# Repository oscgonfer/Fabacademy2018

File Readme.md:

# Fabacademy 2018

This repository is meant to host the week assignments for the fabacademy 2018.

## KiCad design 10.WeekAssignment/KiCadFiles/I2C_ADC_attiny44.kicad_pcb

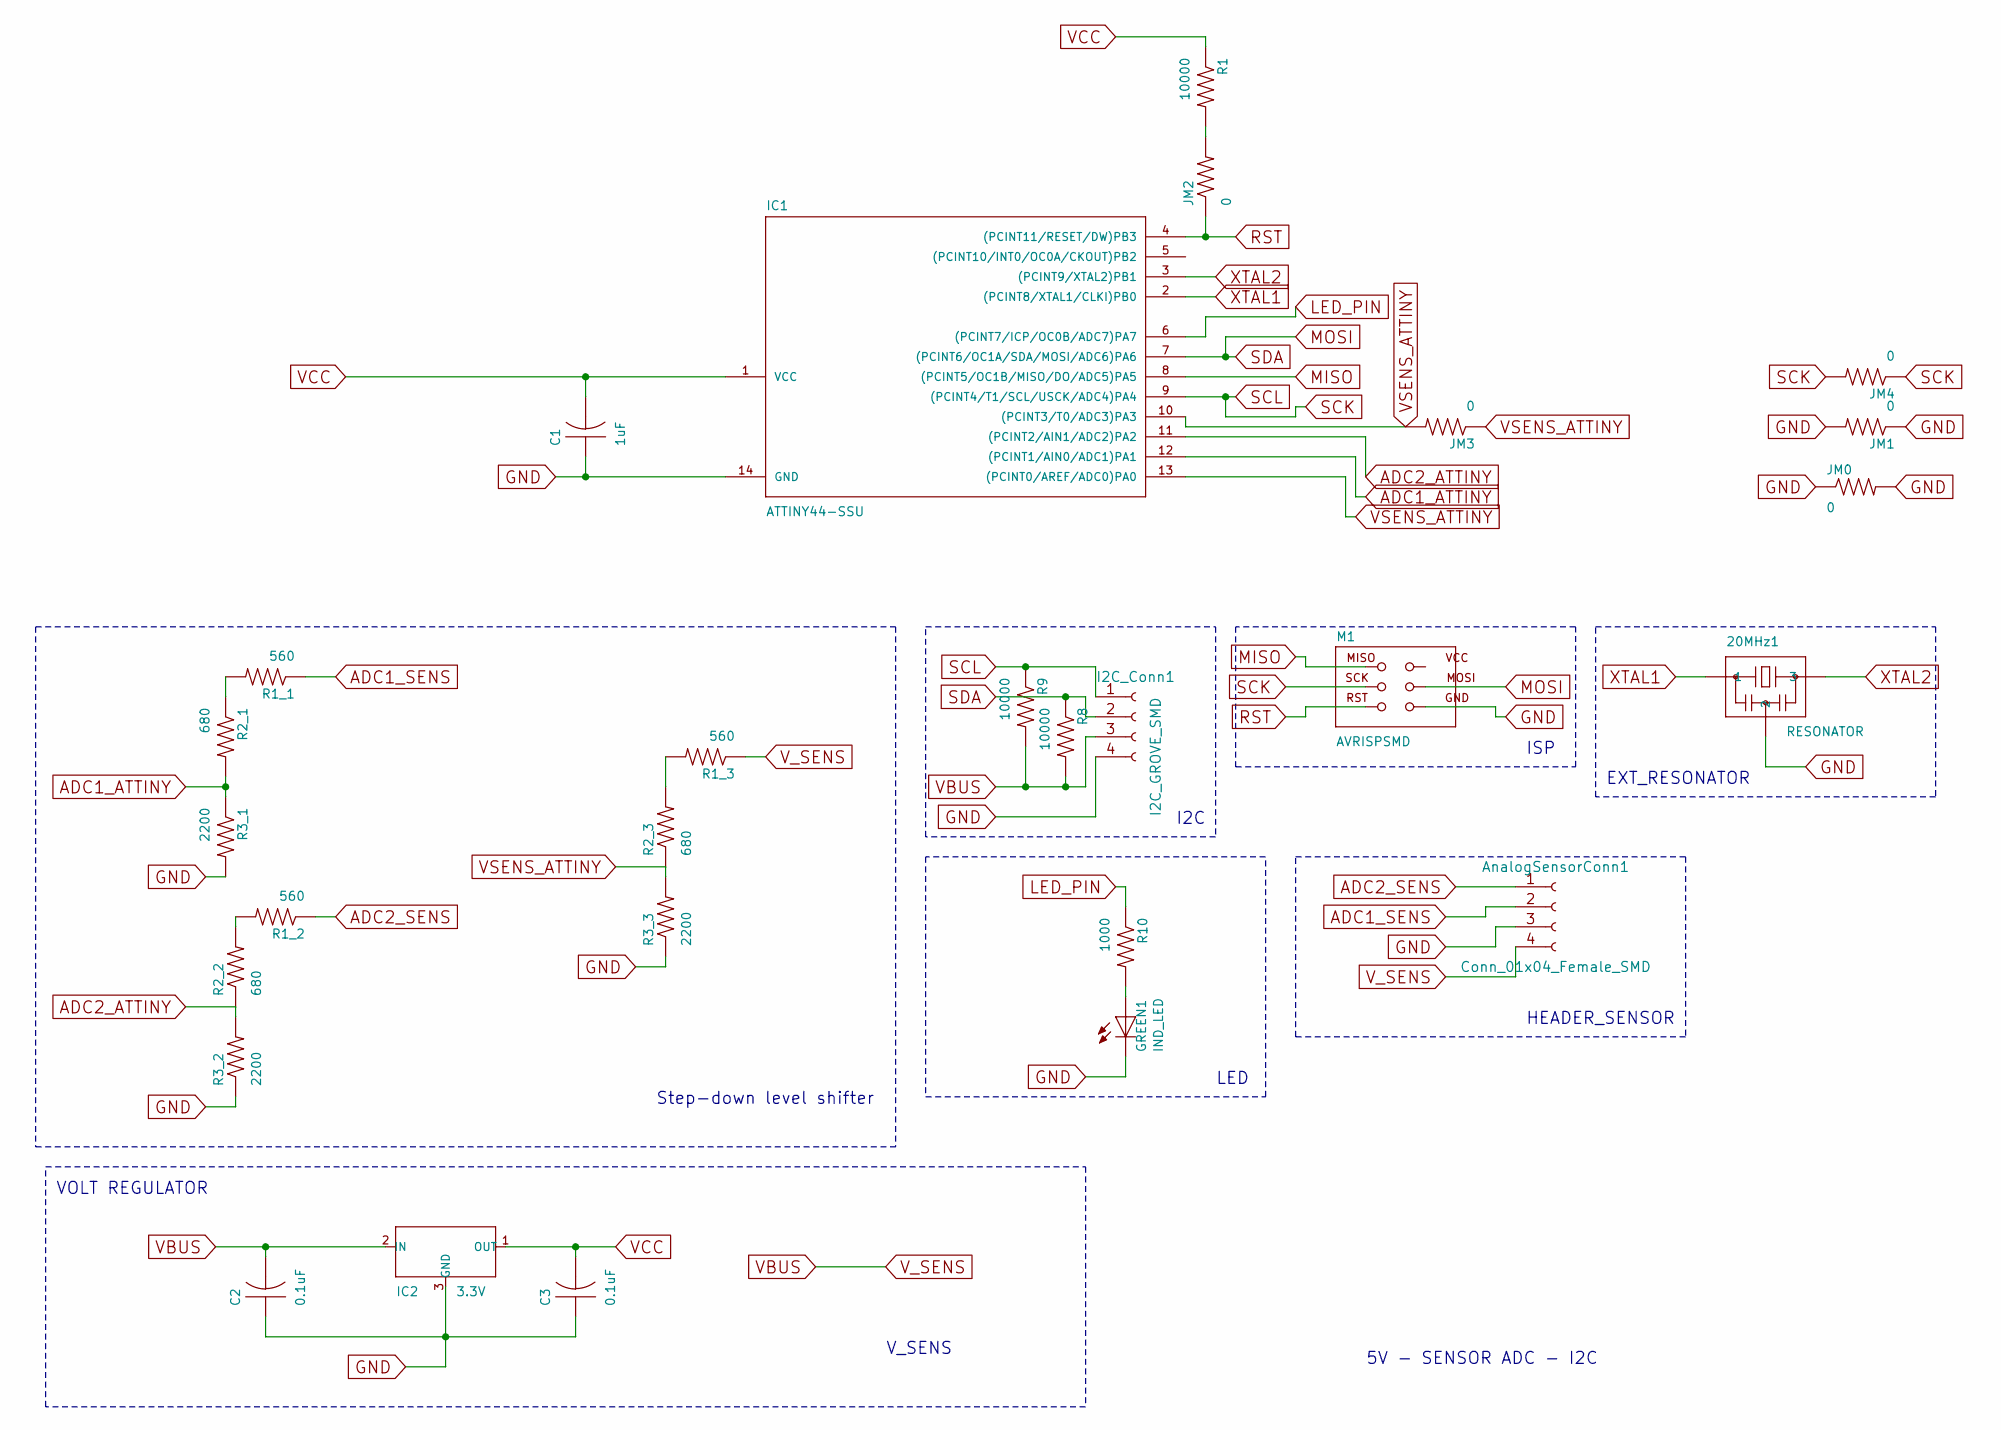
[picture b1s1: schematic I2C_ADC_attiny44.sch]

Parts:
20MHz1: RESONATOR; fab-EFOBM
AnalogSensorConn1: Conn_01x04_Female_SMD; 1X04SMD
C1: 1uF; fab_C1206FAB
C2, C3: 0.1uF; fab-C1206FAB
GREEN1: IND_LED; fab-LED1206FAB
I2C_Conn1: I2C_GROVE_SMD; I2C_GROVE
IC1: ATTINY44-SSU; fab-SOIC14
IC2: 3.3V; fab-SOT23
JM0, JM1, JM2, JM3, JM4: 0; fab-R1206FAB
M1: AVRISPSMD; fab-2X03SMD
R1, R8, R9: 10000; fab-R1206FAB
R1_1, R1_2, R1_3: 560; fab-R1206FAB
R2_1: 680; fab_R1206FAB
R2_2, R2_3: 680; fab-R1206FAB
R3_1, R3_2, R3_3: 2200; fab-R1206FAB
R10: 1000; fab-R1206FAB

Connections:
ADC1_ATTINY: IC1.12 ((PCINT1/AIN0/ADC1)PA1), R2_1.2, R3_1.1
ADC1_SENS: AnalogSensorConn1.2, R1_1.1
ADC2_ATTINY: IC1.11 ((PCINT2/AIN1/ADC2)PA2), R2_2.1, R3_2.2
ADC2_SENS: AnalogSensorConn1.1, R1_2.1
GND: 20MHz1.2, AnalogSensorConn1.3, C1.1, C2.1, C3.1, GREEN1.2 (C), I2C_Conn1.4, IC1.14 (GND), IC2.3 (GND), JM0.1, JM0.2, JM1.1, JM1.2, M1.6 (GND), R3_1.2, R3_2.1, R3_3.1
LED_PIN: IC1.6 ((PCINT7/ICP/OC0B/ADC7)PA7), R10.1
MISO: IC1.8 ((PCINT5/OC1B/MISO/DO/ADC5)PA5), M1.1 (MISO)
MOSI: I2C_Conn1.2, IC1.7 ((PCINT6/OC1A/SDA/MOSI/ADC6)PA6), M1.4 (MOSI), R8.1
unnamed: GREEN1.1 (A), R10.2
unnamed: JM2.2, R1.2
unnamed: R1_1.2, R2_1.1
unnamed: R1_2.2, R2_2.2
unnamed: R1_3.2, R2_3.2
RST: IC1.4 ((PCINT11/RESET/DW)PB3), JM2.1, M1.5 (RST)
SCK: I2C_Conn1.1, IC1.9 ((PCINT4/T1/SCL/USCK/ADC4)PA4), JM4.1, JM4.2, M1.3 (SCK), R9.1
VBUS: AnalogSensorConn1.4, C2.2, I2C_Conn1.3, IC2.2 (IN), R1_3.1, R8.2, R9.2
VCC: C1.2, C3.2, IC1.1 (VCC), IC2.1 (OUT), R1.1
VSENS_ATTINY: IC1.10 ((PCINT3/T0/ADC3)PA3), IC1.13 ((PCINT0/AREF/ADC0)PA0), JM3.1, JM3.2, R2_3.1, R3_3.2
XTAL1: 20MHz1.1, IC1.2 ((PCINT8/XTAL1/CLKI)PB0)
XTAL2: 20MHz1.3, IC1.3 ((PCINT9/XTAL2)PB1)

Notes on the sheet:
VOLT REGULATOR
I2C
HEADER_SENSOR
EXT_RESONATOR
ISP
V_SENS
5V - SENSOR ADC - I2C
Step-down level shifter
LED

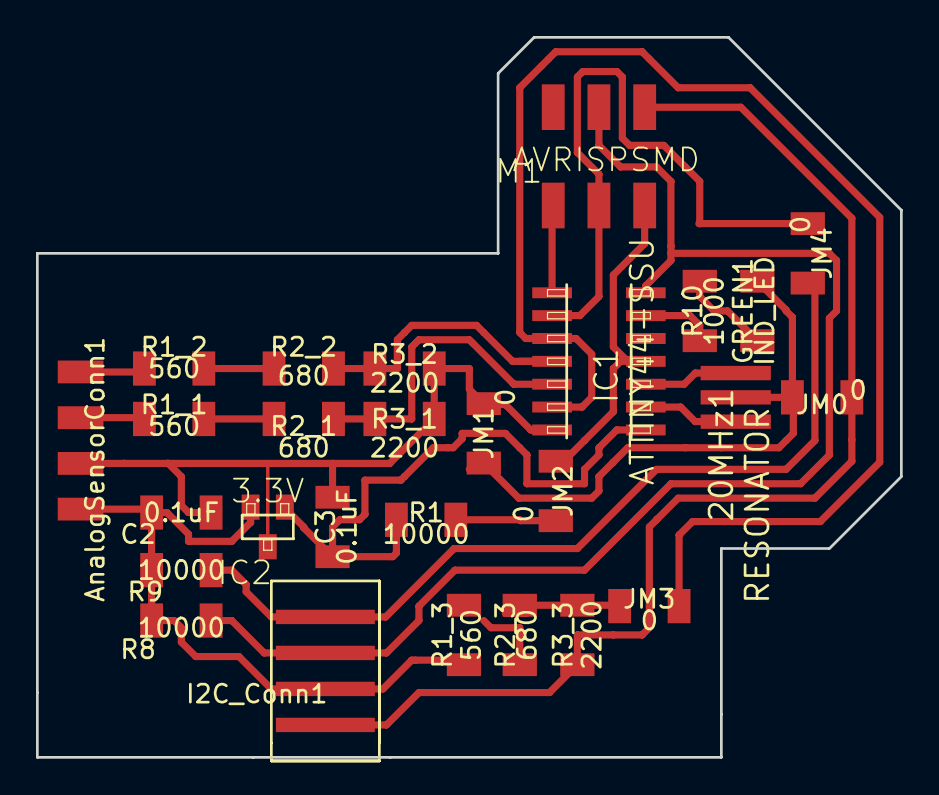
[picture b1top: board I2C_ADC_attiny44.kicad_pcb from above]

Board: 2 copper layers, 48.0 x 40.0 mm, 27 parts (0 on the bottom side), 20 nets.

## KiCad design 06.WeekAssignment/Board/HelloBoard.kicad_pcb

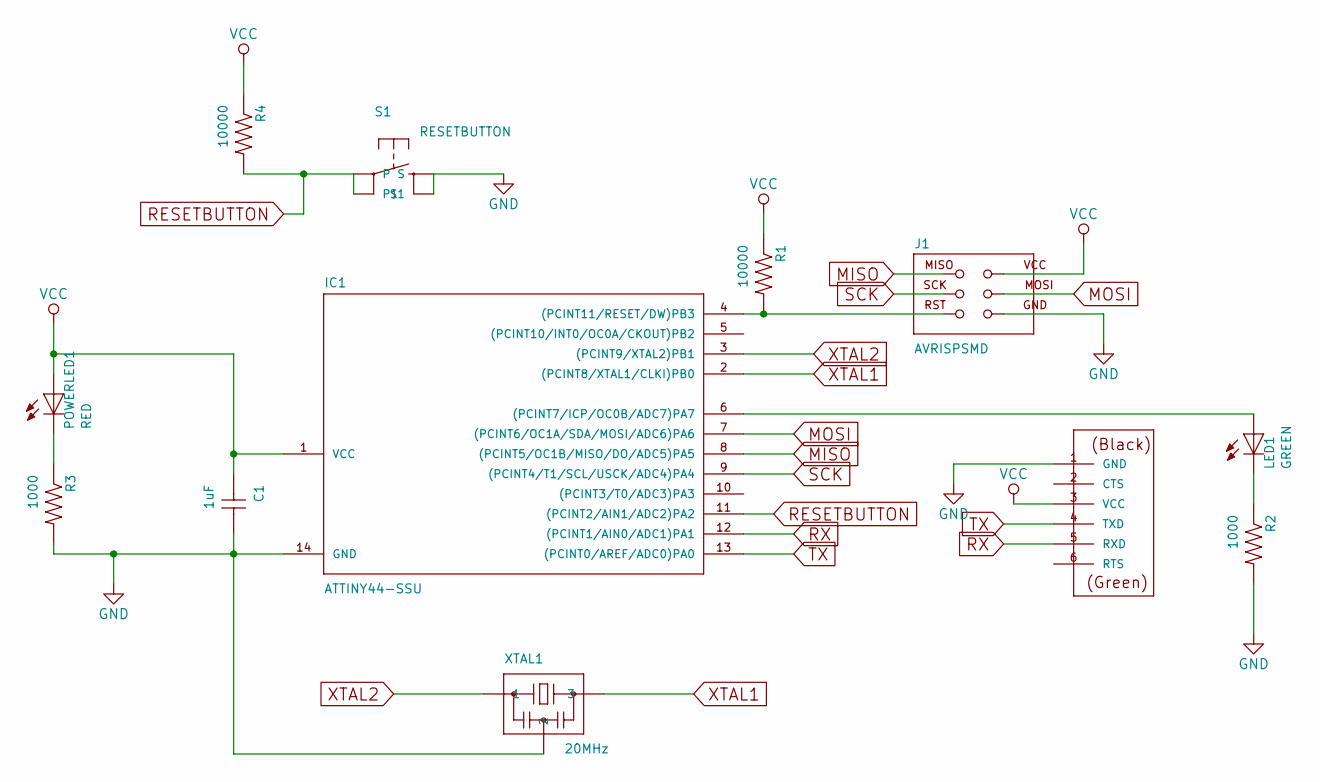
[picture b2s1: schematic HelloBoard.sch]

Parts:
C1: 1uF; C1206FAB
IC1: ATTINY44-SSU; SOIC14
J1: AVRISPSMD; 2X03SMD
J2: FTDI-SMD-HEADER; 1X06SMD
LED1: GREEN; LED1206FAB
POWERLED1: RED; LED1206FAB
R1, R4: 10000; R1206FAB
R2, R3: 1000; R1206FAB
S1: RESETBUTTON; 6MM_SWITCH
XTAL1: 20MHz; EFOBM

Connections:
GND: C1.2, IC1.14 (GND), J1.6 (GND), J2.1 (GND), R2.2, R3.2, S1.3 (S), S1.4 (S1), XTAL1.2
MISO: IC1.8 ((PCINT5/OC1B/MISO/DO/ADC5)PA5), J1.1 (MISO)
MOSI: IC1.7 ((PCINT6/OC1A/SDA/MOSI/ADC6)PA6), J1.4 (MOSI)
unnamed: IC1.4 ((PCINT11/RESET/DW)PB3), J1.5 (RST), R1.2
unnamed: IC1.6 ((PCINT7/ICP/OC0B/ADC7)PA7), LED1.1 (A)
unnamed: LED1.2 (C), R2.1
unnamed: POWERLED1.2 (C), R3.1
RESETBUTTON: IC1.11 ((PCINT2/AIN1/ADC2)PA2), R4.2, S1.1, S1.2 (P1)
RX: IC1.12 ((PCINT1/AIN0/ADC1)PA1), J2.5 (RXD)
SCK: IC1.9 ((PCINT4/T1/SCL/USCK/ADC4)PA4), J1.3 (SCK)
TX: IC1.13 ((PCINT0/AREF/ADC0)PA0), J2.4 (TXD)
VCC: C1.1, IC1.1 (VCC), J1.2 (VCC), J2.3 (VCC), POWERLED1.1 (A), R1.1, R4.1
XTAL1: IC1.2 ((PCINT8/XTAL1/CLKI)PB0), XTAL1.3
XTAL2: IC1.3 ((PCINT9/XTAL2)PB1), XTAL1.1

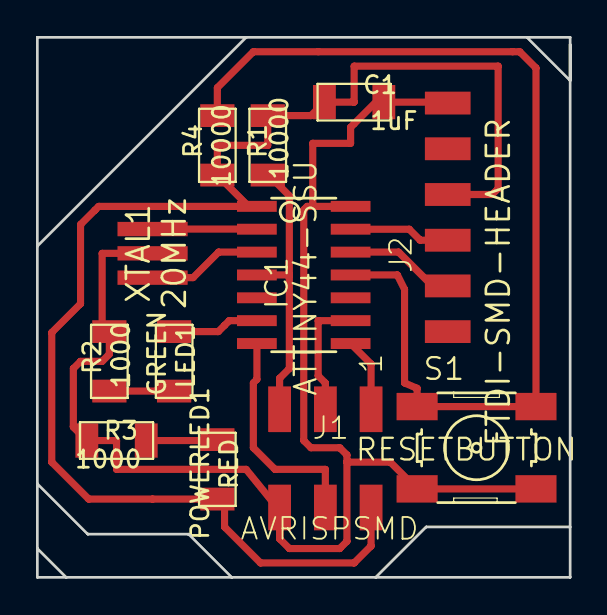
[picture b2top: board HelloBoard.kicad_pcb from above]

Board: 2 copper layers, 29.6 x 30.0 mm, 12 parts (0 on the bottom side), 14 nets.

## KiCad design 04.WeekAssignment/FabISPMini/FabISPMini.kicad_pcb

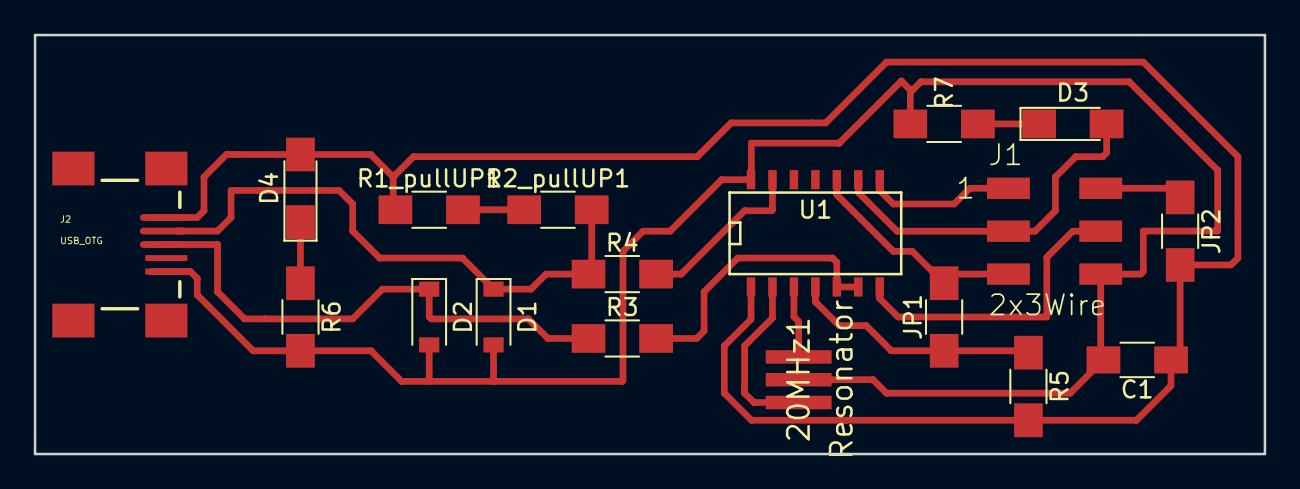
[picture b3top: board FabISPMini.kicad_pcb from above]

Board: 2 copper layers, 72.8 x 24.8 mm, 18 parts (0 on the bottom side), 17 nets.

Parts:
20MHz1: Resonator; EFOBM
C1: 1uF; C_1206_HandSoldering
D1, D2: 3.3V; D_SOD-123
D3: GREEN; LED_1206_HandSoldering
D4: RED; LED_1206_HandSoldering
J1: 2x3Wire; 2X03SMD
J2: USB_OTG; USB_MINIB
JP1, JP2: Jumper; R_1206_HandSoldering
R1_pullUP1, R6: 1k; R_1206_HandSoldering
R2_pullUP1, R7: 499; R_1206_HandSoldering
R3, R4: 100; R_1206_HandSoldering
R5: 10k; R_1206_HandSoldering
U1: ATTINY44A-SSU; SOIC-14_N

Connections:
Earth: 20MHz1.2, C1.2, D1.2, D2.2, J1.6, R6.2, R7.1, U1.14
MISO: J1.1, U1.8
MOSI: J1.4, U1.7
unnamed: D1.1, R2_pullUP1.2, R4.1
unnamed: D2.1, R3.1
unnamed: D3.1, R7.2
unnamed: D4.1, R6.1
unnamed: J1.2, JP2.1
unnamed: JP1.1, R5.1, U1.4
unnamed: R1_pullUP1.2, R2_pullUP1.1
unnamed: R3.2, U1.5, U1.6
unnamed: R4.2, U1.13
RST: J1.5, JP1.2, U1.10
SCK: D3.2, J1.3, U1.9
VCC: C1.1, D4.2, JP2.2, R1_pullUP1.1, R5.2, U1.1
XTAL1: 20MHz1.1, U1.2
XTAL2: 20MHz1.3, U1.3

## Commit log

2018-02-07 2nd week assignment
2018-02-09 Add 02 week rhino exploration
2018-02-13 03 Week assignment
2018-02-21 04 Week Assignment ISP
2018-02-21 Correct files to 74mm
2018-02-26 3D printing assignment
2018-02-26 Add scan
2018-03-05 Electronics design assignment
2018-03-14 Make something big
2018-03-20 Embedded programming
2018-03-25 Semifinal project
2018-04-04 Molding and casting files
2018-04-16 10th Week Assignment Files
